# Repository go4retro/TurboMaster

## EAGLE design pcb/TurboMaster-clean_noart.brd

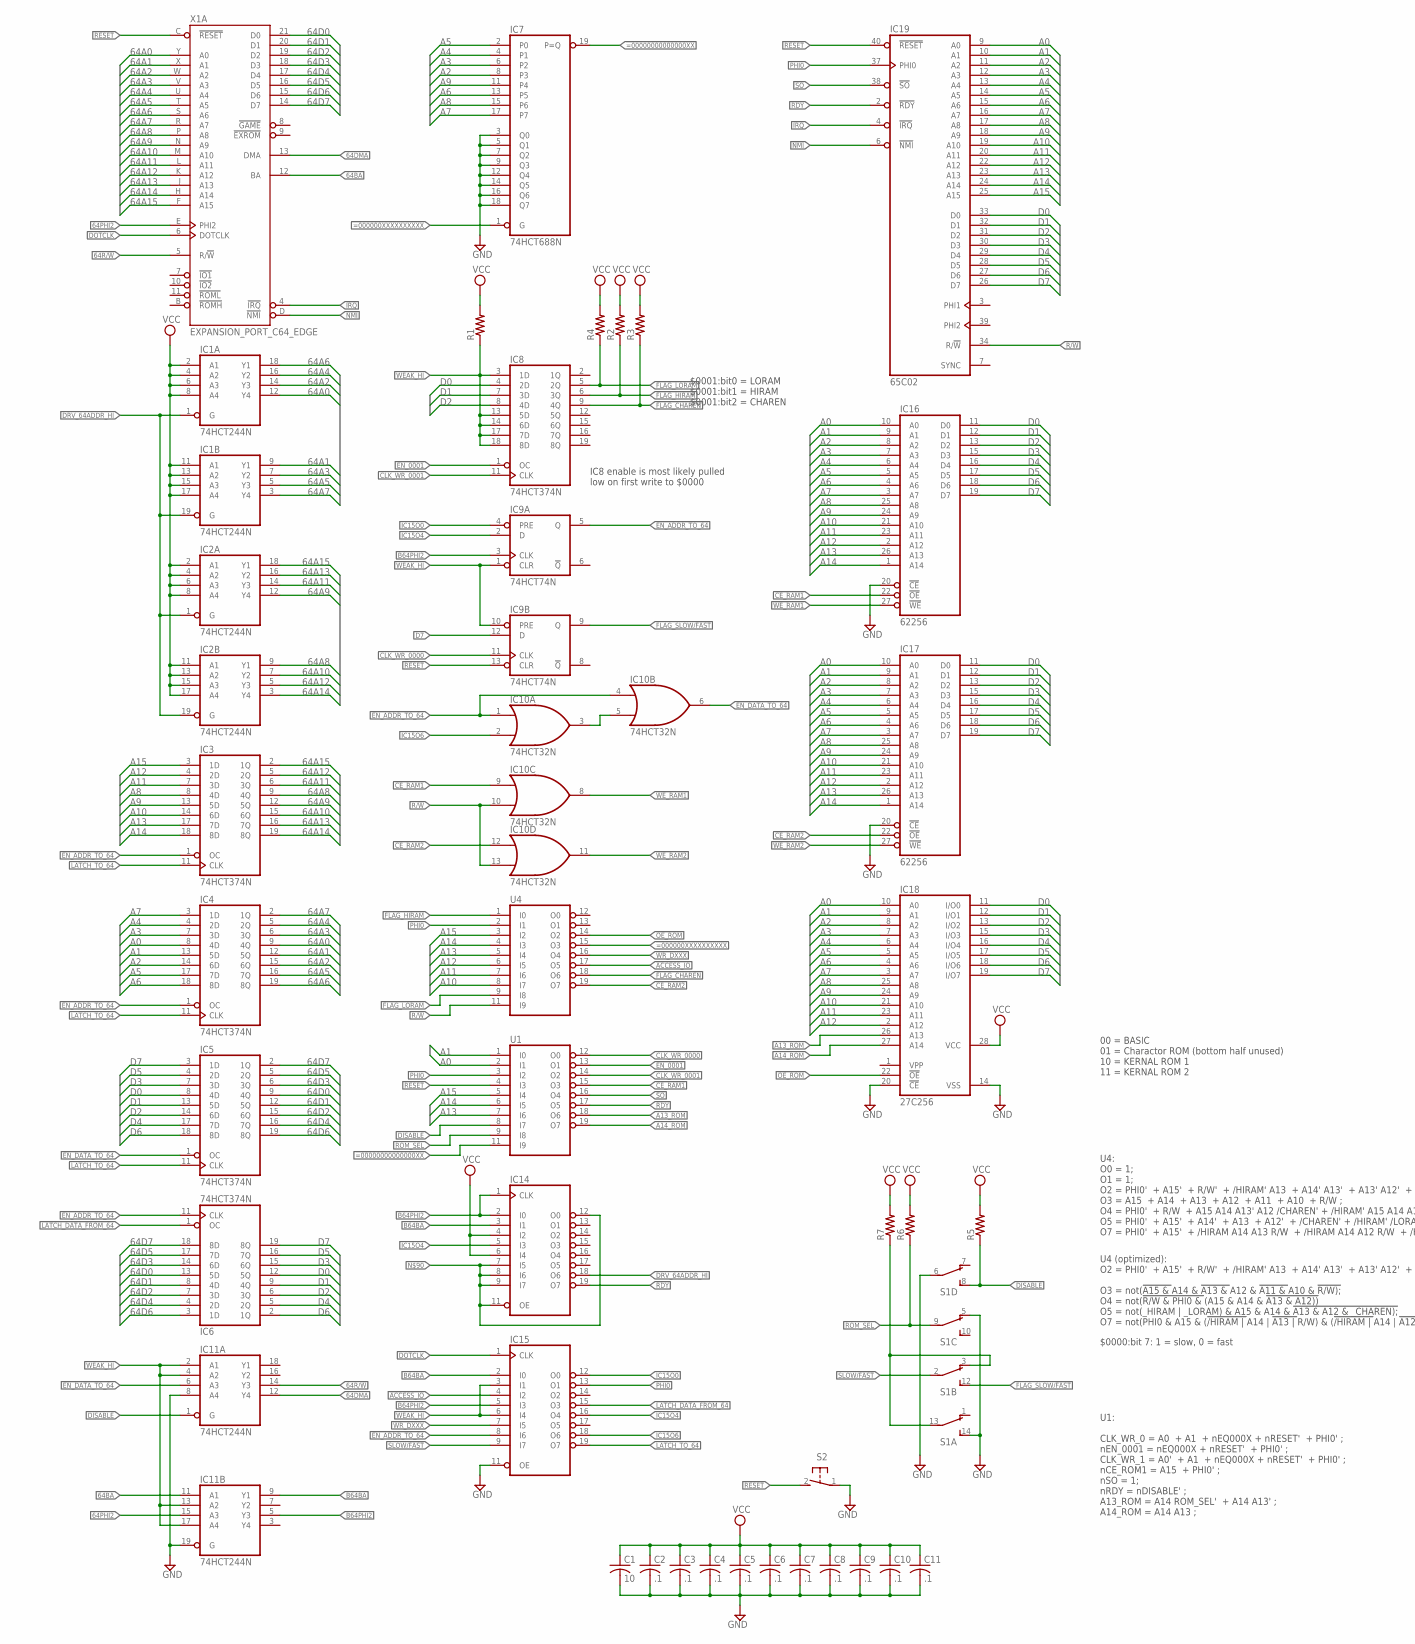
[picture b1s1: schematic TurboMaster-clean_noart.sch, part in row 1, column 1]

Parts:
C1: 10; C050-024X044
C2, C3, C4, C5, C6, C7, C8, C9, C10, C11: .1; C050-024X044
IC1, IC2, IC11: 74HCT244N; DIL20-RP
IC3, IC4, IC5, IC6, IC8: 74HCT374N; DIL20-RP
IC7: 74HCT688N; DIL20-RP
IC9: 74HCT74N; DIL14-RP
IC10: 74HCT32N; DIL14-RP
IC14: 16R4-RP; DIL20-RP
IC15: 16R6-RP; DIL20-RP
IC16, IC17: 62256; DIL28-6-RP
IC18: 27C256; DIL28-6-RP
IC19: 65C02; DIL40-ROUNDPAD
R1, R2, R3, R4, R5, R6, R7: R-US_0207/10; 0207/10
S1: DIP04DPDTS-RP
S2: 31-XX; B3F-31XX
U1, U4: 16L8-RP; DIL20-RP
X1: EXPANSION_PORT_C64_EDGE; MA100-22-2

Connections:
64A0: IC1.12 (Y4), IC4.9 (4Q), X1.Y (A0)
64A1: IC1.9 (Y1), IC4.12 (5Q), X1.X (A1)
64A2: IC1.14 (Y3), IC4.15 (6Q), X1.W (A2)
64A3: IC1.7 (Y2), IC4.6 (3Q), X1.V (A3)
64A4: IC1.16 (Y2), IC4.5 (2Q), X1.U (A4)
64A5: IC1.5 (Y3), IC4.16 (7Q), X1.T (A5)
64A6: IC1.18 (Y1), IC4.19 (8Q), X1.S (A6)
64A7: IC1.3 (Y4), IC4.2 (1Q), X1.R (A7)
64A8: IC2.9 (Y1), IC3.9 (4Q), X1.P (A8)
64A9: IC2.12 (Y4), IC3.12 (5Q), X1.N (A9)
64A10: IC2.7 (Y2), IC3.15 (6Q), X1.M (A10)
64A11: IC2.14 (Y3), IC3.6 (3Q), X1.L (A11)
64A12: IC2.5 (Y3), IC3.5 (2Q), X1.K (A12)
64A13: IC2.16 (Y2), IC3.16 (7Q), X1.J (A13)
64A14: IC2.3 (Y4), IC3.19 (8Q), X1.H (A14)
64A15: IC2.18 (Y1), IC3.2 (1Q), X1.F (A15)
64BA: IC11.11 (A1), X1.12 (BA)
64D0: IC5.9 (4Q), IC6.13 (5D), X1.21 (D0)
64D1: IC5.12 (5Q), IC6.8 (4D), X1.20 (D1)
64D2: IC5.15 (6Q), IC6.7 (3D), X1.19 (D2)
64D3: IC5.6 (3Q), IC6.14 (6D), X1.18 (D3)
64D4: IC5.16 (7Q), IC6.4 (2D), X1.17 (D4)
64D5: IC5.5 (2Q), IC6.17 (7D), X1.16 (D5)
64D6: IC5.19 (8Q), IC6.3 (1D), X1.15 (D6)
64D7: IC5.2 (1Q), IC6.18 (8D), X1.14 (D7)
64DMA: IC11.12 (Y4), X1.13 (DMA)
64PHI2: IC11.15 (A3), X1.E (PHI2)
64R/!W: IC11.14 (Y3), X1.5 (R/!W)
!=00000000000000XX: IC7.19 (P=Q), U1.11 (I9)
!=000000XXXXXXXXXX: IC7.1 (G), U4.15 (O3)
!ACCESS_IO: IC15.4 (I2), U4.17 (O5)
!CE_RAM1: IC10.9 (I0), IC16.22 (!OE), U1.15 (O3)
!CE_RAM2: IC10.12 (I0), IC17.22 (!OE), U4.19 (O7)
!EN_0001: IC8.1 (OC), U1.13 (O1)
!EN_ADDR_TO_64: IC3.1 (OC), IC4.1 (OC), IC6.11 (CLK), IC9.5 (Q), IC10.1 (I0), IC10.4 (I0), IC15.8 (I6)
!EN_DATA_TO_64: IC5.1 (OC), IC10.6 (O), IC11.6 (A3)
!FLAG_CHAREN: IC8.9 (4Q), R3.1, U4.18 (O6)
!FLAG_HIRAM: IC8.6 (3Q), R2.1, U4.1 (I0)
!FLAG_LORAM: IC8.5 (2Q), R4.1, U4.9 (I8)
!IRQ: IC19.4 (!IRQ), X1.4 (!IRQ)
!LATCH_DATA_FROM_64: IC6.1 (OC), IC15.15 (O3)
!NMI: IC19.6 (!NMI), X1.D (!NMI)
!OE_ROM: IC18.22 (!OE), U4.14 (O2)
!RDY: IC14.19 (O7), IC19.2 (!RDY), U1.17 (O5)
!RESET: IC9.13 (CLR), IC19.40 (!RESET), S2.2 (S), U1.4 (I3), X1.C (!RESET)
!SO: IC19.38 (!SO), U1.16 (O4)
!WE_RAM1: IC10.8 (O), IC16.27 (!WE)
!WE_RAM2: IC10.11 (O), IC17.27 (!WE)
!WR_DXXX: IC15.7 (I5), U4.16 (O4)
A0: IC4.8 (4D), IC16.10 (A0), IC17.10 (A0), IC18.10 (A0), IC19.9 (A0), U1.2 (I1)
A1: IC4.13 (5D), IC16.9 (A1), IC17.9 (A1), IC18.9 (A1), IC19.10 (A1), U1.1 (I0)
A2: IC4.14 (6D), IC7.8 (P3), IC16.8 (A2), IC17.8 (A2), IC18.8 (A2), IC19.11 (A2)
A3: IC4.7 (3D), IC7.6 (P2), IC16.7 (A3), IC17.7 (A3), IC18.7 (A3), IC19.12 (A3)
A4: IC4.4 (2D), IC7.4 (P1), IC16.6 (A4), IC17.6 (A4), IC18.6 (A4), IC19.13 (A4)
A5: IC4.17 (7D), IC7.2 (P0), IC16.5 (A5), IC17.5 (A5), IC18.5 (A5), IC19.14 (A5)
A6: IC4.18 (8D), IC7.13 (P5), IC16.4 (A6), IC17.4 (A6), IC18.4 (A6), IC19.15 (A6)
A7: IC4.3 (1D), IC7.17 (P7), IC16.3 (A7), IC17.3 (A7), IC18.3 (A7), IC19.16 (A7)
A8: IC3.8 (4D), IC7.15 (P6), IC16.25 (A8), IC17.25 (A8), IC18.25 (A8), IC19.17 (A8)
A9: IC3.13 (5D), IC7.11 (P4), IC16.24 (A9), IC17.24 (A9), IC18.24 (A9), IC19.18 (A9)
A10: IC3.14 (6D), IC16.21 (A10), IC17.21 (A10), IC18.21 (A10), IC19.19 (A10), U4.8 (I7)
A11: IC3.7 (3D), IC16.23 (A11), IC17.23 (A11), IC18.23 (A11), IC19.20 (A11), U4.7 (I6)
A12: IC3.4 (2D), IC16.2 (A12), IC17.2 (A12), IC18.2 (A12), IC19.22 (A12), U4.6 (I5)
A13: IC3.17 (7D), IC16.26 (A13), IC17.26 (A13), IC19.23 (A13), U1.7 (I6), U4.5 (I4)
A13_ROM: IC18.26 (A13), U1.18 (O6)
A14: IC3.18 (8D), IC16.1 (A14), IC17.1 (A14), IC19.24 (A14), U1.6 (I5), U4.4 (I3)
A14_ROM: IC18.27 (A14), U1.19 (O7)
A15: IC3.3 (1D), IC19.25 (A15), U1.5 (I4), U4.3 (I2)
B64BA: IC11.9 (Y1), IC14.3 (I1), IC15.2 (I0)
B64PHI2: IC9.3 (CLK), IC11.5 (Y3), IC14.1 (CLK), IC14.2 (I0), IC15.5 (I3)
CLK_WR_0000: IC9.11 (CLK), U1.12 (O0)
CLK_WR_0001: IC8.11 (CLK), U1.14 (O2)
D0: IC5.8 (4D), IC6.12 (5Q), IC8.4 (2D), IC16.11 (D0), IC17.11 (D0), IC18.11 (I/O0), IC19.33 (D0)
D1: IC5.13 (5D), IC6.9 (4Q), IC8.7 (3D), IC16.12 (D1), IC17.12 (D1), IC18.12 (I/O1), IC19.32 (D1)
D2: IC5.14 (6D), IC6.6 (3Q), IC8.8 (4D), IC16.13 (D2), IC17.13 (D2), IC18.13 (I/O2), IC19.31 (D2)
D3: IC5.7 (3D), IC6.15 (6Q), IC16.15 (D3), IC17.15 (D3), IC18.15 (I/O3), IC19.30 (D3)
D4: IC5.17 (7D), IC6.5 (2Q), IC16.16 (D4), IC17.16 (D4), IC18.16 (I/O4), IC19.29 (D4)
D5: IC5.4 (2D), IC6.16 (7Q), IC16.17 (D5), IC17.17 (D5), IC18.17 (I/O5), IC19.28 (D5)
D6: IC5.18 (8D), IC6.2 (1Q), IC16.18 (D6), IC17.18 (D6), IC18.18 (I/O6), IC19.27 (D6)
D7: IC5.3 (1D), IC6.19 (8Q), IC9.12 (D), IC16.19 (D7), IC17.19 (D7), IC18.19 (I/O7), IC19.26 (D7)
DISABLE: IC11.1 (G), R5.1, S1.8 (S), U1.8 (I7)
DOTCLK: IC15.1 (CLK), X1.6 (DOTCLK)
DRV_64ADDR_HI: IC1.1 (G), IC1.19 (G), IC2.1 (G), IC2.19 (G), IC14.18 (O6)
FLAG_SLOW/!FAST: IC9.9 (Q), S1.12 (S)
GND: C1.2, C2.2, C3.2, C4.2, C5.2, C6.2, C7.2, C8.2, C9.2, C10.2, C11.2, IC1.10 (GND), IC2.10 (GND), IC3.10 (GND), IC4.10 (GND), IC5.10 (GND), IC6.10 (GND), IC7.3 (Q0), IC7.5 (Q1), IC7.7 (Q2), IC7.9 (Q3), IC7.10 (GND), IC7.12 (Q4), IC7.14 (Q5), IC7.16 (Q6), IC7.18 (Q7), IC8.10 (GND), IC9.7 (GND), IC10.7 (GND), IC11.8 (A4), IC11.10 (GND), IC11.19 (G), IC14.10 (GND), IC15.10 (GND), IC15.11 (OE), IC16.14 (GND), IC16.20 (!CE), IC17.14 (GND), IC17.20 (!CE), IC18.14 (VSS), IC18.20 (!CE), IC19.1 (GND), IC19.21 (GND), S1.5 (O), S1.6, S1.14 (S), S2.1, U1.10 (GND), U4.10 (GND), X1.1 (GND), X1.22 (GND), X1.A (GND), X1.Z (GND)
IC15O0: IC9.4 (PRE), IC15.12 (O0)
IC15O4: IC9.2 (D), IC14.5 (I3), IC15.16 (O4)
IC15O6: IC10.2 (I1), IC15.18 (O6)
LATCH_TO_64: IC3.11 (CLK), IC4.11 (CLK), IC5.11 (CLK), IC15.19 (O7)
unnamed: R7.1, S1.3 (O), S1.13
unnamed: IC10.3 (O), IC10.5 (I1)
unnamed: IC14.7 (I5), IC14.8 (I6), IC14.9 (I7), IC14.11 (OE), IC14.12 (O0)
PHI0: IC15.13 (O1), IC19.37 (PHI0), U1.3 (I2), U4.2 (I1)
R/!W: IC10.10 (I1), IC10.13 (I1), IC19.34 (R/!W), U4.11 (I9)
ROM_SEL: R6.1, S1.9, U1.9 (I8)
SLOW/!FAST: IC15.9 (I7), S1.2
VCC: C1.1, C2.1, C3.1, C4.1, C5.1, C6.1, C7.1, C8.1, C9.1, C10.1, C11.1, IC1.2 (A1), IC1.4 (A2), IC1.6 (A3), IC1.8 (A4), IC1.11 (A1), IC1.13 (A2), IC1.15 (A3), IC1.17 (A4), IC1.20 (VCC), IC2.2 (A1), IC2.4 (A2), IC2.6 (A3), IC2.8 (A4), IC2.11 (A1), IC2.13 (A2), IC2.15 (A3), IC2.17 (A4), IC2.20 (VCC), IC3.20 (VCC), IC4.20 (VCC), IC5.20 (VCC), IC6.20 (VCC), IC7.20 (VCC), IC8.20 (VCC), IC9.14 (VCC), IC10.14 (VCC), IC11.20 (VCC), IC14.4 (I2), IC14.6 (I4), IC14.20 (VCC), IC15.20 (VCC), IC16.28 (VCC), IC17.28 (VCC), IC18.28 (VCC), IC19.8 (VCC), R1.2, R2.2, R3.2, R4.2, R5.2, R6.2, R7.2, U1.20 (VCC), U4.20 (VCC), X1.2 (VCC), X1.3 (VCC)
WEAK_HI: IC8.3 (1D), IC8.13 (5D), IC8.14 (6D), IC8.17 (7D), IC8.18 (8D), IC9.1 (CLR), IC9.10 (PRE), IC11.2 (A1), IC11.4 (A2), IC11.13 (A2), IC11.17 (A4), IC15.3 (I1), IC15.6 (I4), R1.1

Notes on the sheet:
00 = BASIC 01 = Charactor ROM (bottom half unused) 10 = KERNAL ROM 1 11 = KERNAL ROM 2
$0001:bit0 = LORAM $0001:bit1 = HIRAM $0001:bit2 = CHAREN
IC8 enable is most likely pulled low on first write to $0000
Reverse Engineered by: Jim Brain
$0000:bit 7: 1 = slow, 0 = fast
U4: O0 = 1; O1 = 1; O2 = PHI0' + A15' + R/W' + /HIRAM' A13 + A14' A13' + A13' A12' + /HIRAM' /LORAM' + A14' /LORAM' + A13' /CHAREN; O3 = A15 + A14 + A13 + A12 + A11 + A10 + R/W ; O4 = PHI0' + R/W + A15 A14 A13' A12 /CHAREN' + /HIRAM' A15 A14 A13' A12 /LORAM' ; O5 = PHI0' + A15' + A14' + A13 + A12' 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
U1: CLK_WR_0 = A0 + A1 + nEQ000X + nRESET' + PHI0' ; nEN_0001 = nEQ000X + nRESET' + PHI0' ; CLK_WR_1 = A0' + A1 + nEQ000X + nRESET' + PHI0' ; nCE_ROM1 = A15 + PHI0' ; nSO = 1; nRDY = nDISABLE' ; A13_ROM = A14 ROM_SEL' + A14 A13' ; A14_ROM = A14 A13 ;
U4 (optimized): O2 = PHI0' + A15' + R/W' + /HIRAM' A13 + A14' A13' + A13' A12' + /HIRAM' /LORAM' + A14' /LORAM' + A13' /CHAREN; O3 = not(!A15 & !A14 & !A13 & !A12 & !A11 & !A10 & !R/W); O4 = not(!R/W & PHI0 & !(A15 & A14 & !A13 & A12)) O5 = not(_HIRAM | _LORAM) & A15 & A14 & !A13 & A12 & _CHAREN); 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

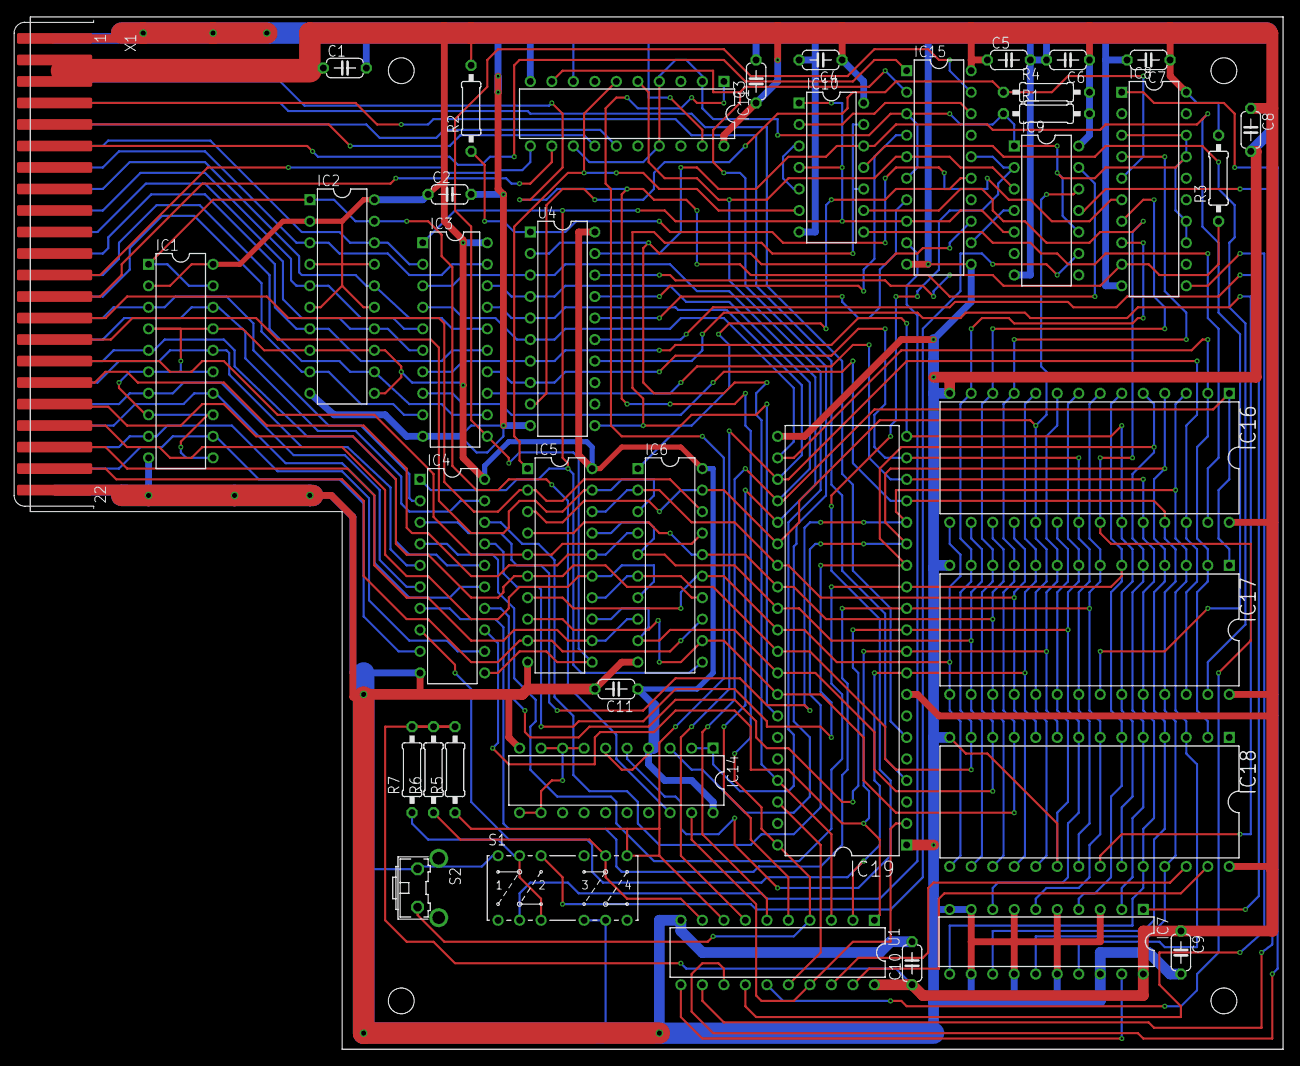
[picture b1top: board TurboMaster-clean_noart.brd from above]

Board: 2 copper layers, 148.0 x 121.9 mm, 40 parts (0 on the bottom side), 97 nets.

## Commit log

2020-07-08 Added Debugging.pdn to verify correct PCB design
2020-07-09 Added higher resolution PCB images for comparison
2020-07-11 Schematic signal naming updates
2020-07-11 Confirmed working U1 equations and PLD files.
2020-07-15 Working U1 and U4 JED files
2020-07-15 Filename issue
2020-08-09 Fixed bus in u1 HDL
